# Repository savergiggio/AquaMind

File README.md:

<p align="center">
  <strong>The brain of your aquarium. 🐟</strong><br>
  Real-time monitoring: <strong>temp, pH, TDS, level, camera, AI, notifications</strong>.
</p>

<p align="center">
  <strong>🇬🇧 English</strong> · <a href="README_it.md"><strong>🇮🇹 Italiano</strong></a>
</p>

<p align="center">

</p>

<p align="center">
  <sub>
  <a href="#-features">Features</a> ·
  <a href="#-web-ui-react-dashboard">Web UI</a> ·
  <a href="#-mobile-app">Mobile app</a> ·
  <a href="#-architecture">Architecture</a> ·
  <a href="#-repository-structure">Contents</a> ·
  <a href="#-3d-models-renders">3D models</a> ·
  <a href="#-quick-start">Quick start</a> ·
  <a href="#-api">API</a> ·
  <a href="#-components">Components</a> ·
  <a href="#-sponsor--pcbway">Sponsor · PCBWay</a>
  </sub>
</p>

---

# 🇬🇧 AquaMind

## 🏭 Sponsor · PCBWay

<p align="center">
  
</p>

A big thanks to  **[PCBWay](https://pcbway.com)** for supporting the project and taking care of the PCB fabrication for AquaMind.
They manufactured the AquaMind board directly from the Gerber files and production data available in pcb/kicad/.
I was really happy with how the board turned out. The overall finish was very clean, the silkscreen was sharp, and the drilling and routing looked precise.

The whole production process was straightforward, and the board arrived quickly and well made. Most importantly, the final result matched the design very closely, which gave me much more confidence in the hardware.
Overall, I had a very positive experience with PCBWay. Seeing AquaMind go from a PCB layout on screen to a real, professionally manufactured board was one of the most satisfying parts of the project.

Thanks again to PCBWay for supporting AquaMind and helping turn the design into a real PCB.

- 📂 Fab-ready Gerbers: `pcb/kicad/gerber/`
- 📋 BOM + positions + IPC netlist: `pcb/kicad/production/`
- 🧊 3D model of the board: `pcb/kicad/AquaMind.step`

Want to build the board? Upload the Gerber set to PCBWay — the project thanks
everyone who supports the hardware pipeline. 🐟

---

## 🐟 What is AquaMind

**AquaMind** is a complete, open-source system for monitoring and controlling a
fish tank. A microcontroller reads the submerged sensors, a Raspberry Pi acts as the
central brain (history, video, AI and notifications) and a web dashboard + mobile app
let you keep an eye on everything, even from afar.

The project covers **the entire chain**: from the sensor firmware, to the custom PCB,
to the 3D-printed case, all the way to the Docker backend and the React frontend.

### 📸 The built prototype · 3D-printed case + custom PCB

A photo tour of the **physically built prototype**: PCB fabricated by PCBWay, 3D-printed enclosure and all the components. **Click any photo to open it full size.**

<table>
  <tr>
    <td align="center"><br><sub>🏭 PCB fabricated by PCBWay</sub></td>
    <td align="center"><br><sub>🧩 Components &amp; JST connectors</sub></td>
    <td align="center"><br><sub>🔌 Wired sensors + ESP32</sub></td>
  </tr>
  <tr>
    <td align="center"><br><sub>🧊 3D-printed enclosure + PCB</sub></td>
    <td align="center"><br><sub>🖥️ Enclosure with OLED display</sub></td>
    <td align="center"><br><sub>🐟 3D-printed lid "AQUAMIND"</sub></td>
  </tr>
  <tr>
    <td align="center"><br><sub>🏷️ Front panel · TEMP · PH · TDS · LEVEL</sub></td>
    <td align="center"><br><sub>📂 Open enclosure, PCB inside</sub></td>
    <td align="center"><br><sub>🐠 The prototype in the aquarium</sub></td>
  </tr>
</table>

### ⚙️ Features

| Area | What it does |
|------|-------------|
| 📷 **Video** | **IMX179** camera (8MP, 1080p) inside a **repurposed transparent garden sphere**, live MJPEG streaming |
| 💡 **Controls** | Lights, pump, skimmer, heater, feeder — from web and app |
| 📅 **Scheduler** | Automatic on/off schedules for every device |
| 🤖 **AI** | **Google Gemini** integration for diagnostics and control |
| 🔔 **Notifications** | **ntfy** and **Telegram** alerts when a parameter goes out of range |
| 📈 **History** | Archived data with browsable history (`/sensors/history` API) |
| 🖥️ **Web UI** | **React + Vite + Tailwind** dashboard served by Nginx |
| 📱 **Mobile app** | Android app riding on the **same REST API** (sensors, video, AI, guides, backup) |
| 🧩 **Home Assistant** | Custom component for **Chihiros** lights (BLE) |

---

## 🖥️ Web UI (React dashboard)

The React dashboard is the control center: live video from the underwater sphere,
real-time sensor cards, AI agent, manual controls, schedules, maintenance calendar,
fish inventory and full history. **Click any screenshot to open it full size.**

<table>
  <tr>
    <td align="center" colspan="2"><br><sub>📷 <b>Dashboard</b> — live video, sensors (TEMP · PH · TDS · LEVEL), AquaMind AI agent, manual controls</sub></td>
  </tr>
  <tr>
    <td align="center"><br><sub>📅 <b>Maintenance</b> — calendar with scheduled water changes and events</sub></td>
    <td align="center"><br><sub>💧 <b>Water parameters</b> — full analysis, hardness, complete recipe</sub></td>
  </tr>
  <tr>
    <td align="center"><br><sub>🐠 <b>Fish inventory</b> — species, quantity, food and last feeding</sub></td>
    <td align="center"><br><sub>📈 <b>History</b> — telemetry charts with min/max/avg statistics</sub></td>
  </tr>
</table>

---

## 📱 Mobile app

The **Android app** rides on the same REST API as the dashboard: sensor cards, live video,
AI assistant, treatment guides, tank management and backup — right from the phone.
**Tap any screenshot to open it full size.**

<table>
  <tr>
    <td align="center"><br><sub>🏠 <b>Home</b> — sensor cards (TEMP · PH · TDS · LEVEL), trend charts, AI agent</sub></td>
    <td align="center"><br><sub>📖 <b>Guides &amp; recipes</b> — disease treatments saved per tank</sub></td>
    <td align="center"><br><sub>⚙️ <b>Management</b> — add aquarium, tank manager, backup export/import</sub></td>
    <td align="center"><br><sub>🤖 <b>AI Assistant</b> — Gemini chat, quick diagnostic</sub></td>
    <td align="center"><br><sub>🩺 <b>Full diagnostic</b> — pH, nitrogen cycle, GH/KH, TDS, fish compatibility</sub></td>
  </tr>
</table>

All 12 app screenshots are in [`images/`](images/).

---

## 🧠 Architecture

The flow is simple: the **ESP32-S3** reads the sensors and publishes them as JSON over
serial; the **Raspberry Pi** (in Docker) receives and stores them, acts as the hub for
video and controls, and pushes events to the dashboard, the app and the notification
channels.

```mermaid
flowchart LR
  subgraph Tank
    S1[DS18B20]
    S2[PH-4502C]
    S3[TDS]
    S4[RCWL-1670]
    CAM[IMX179]
  end
  S1 --> ESP[ESP32-S3]
  S2 --> ESP
  S3 --> ESP
  S4 --> ESP
  ESP -- serial JSON --> RPI[Raspberry Pi]
  CAM -- MJPEG --> RPI
  RPI --> DB[(SQLite)]
  RPI --> WEB[React Dashboard]
  RPI --> APP[Mobile App]
  RPI --> AI[Gemini AI]
  RPI --> NTF[ntfy / Telegram]
```

---

## 📦 Repository structure

The repo is organized in 4 areas, one per "layer" of the project:

```
.
├── 3D/
│   ├── case/            #    Enclosure: base, lid, sensor mounts, spacer, cap
│   ├── display/         #    display_aquamind + 53 mm glass mount (SLDPRT/STEP)
│   └── completo/        #    Main assemblies as GLB (viewable in the browser)
├── codice/
│   ├── esp32-s3/        # Sensor firmware (ESP32-S3, v2.0.0-S3)
│   └── raspberry/       # Full dockerized system (backend + frontend)
│       ├── backend/     #   Node.js: API, history, video, AI, notifications, Chihiros
│       ├── frontend/    #   React + Vite + Tailwind (dashboard)
│       ├── docs/        #   Setup notes (Bluetooth, etc.)
│       └── docker-compose.yml
├── pcb/
│   └── kicad/           # KiCad project: sch, pcb, gerber, BOM, netlist, positions
│       ├── gerber/      #   Production files (fab-ready)
│       └── production/  #   BOM, designators, IPC netlist, positions
├── rendering/           # Full-system renderings
├── images/              # Built-prototype photos · Web UI screens · mobile app screens
└── docs/                # Page images and banner
```

### 🧊 1 · Case and 3D models

The mechanics are designed in **SolidWorks** (`.SLDPRT` sources) and exported as
**STEP** (neutral format for CAD/verification). In the repo you will find:

- **`3D/case/`** — the complete enclosure: base, lid, sensor mounts, spacer, cap and
  the full assembly (`AquaMind.step`).
- **`3D/display/`** — the **display housing** (`display_aquamind`) and the **53 mm
  glass mount**, the bracket that fixes the camera sphere to the tank glass.
- **`3D/completo/`** — the **main assemblies as GLB**, viewable directly in the
  browser.

> 💡 `.SLDPRT` are the SolidWorks sources, `.STEP` is the neutral exchange format.

### 🔲 2 · Sensor firmware (ESP32-S3)

`codice/esp32-s3/Aquamind-s3.ino` — firmware that reads the 4 sensors and publishes
them as JSON over serial/UART every 2 seconds, with a **local OLED display** and
**EEPROM-based calibration** (pH offset, TDS coefficient, level range).

- **DS18B20** → temperature (OneWire)
- **PH-4502C** → pH (ADC)
- **TDS** → salinity (ADC)
- **RCWL-1670** → water level (mmWave)
- **SSD1306** → 128×64 OLED display (I²C)

### 🍓 3 · Raspberry Pi system (Docker)

`codice/raspberry/` is the complete **dockerized** system (backend + frontend in
containers):

- **`backend/`** — **Node.js** server: REST API, serial ingest, MJPEG video streaming,
  SQLite history, controls, scheduler, **Gemini AI** proxy, **ntfy/Telegram**
  notifications and a daemon for the **Chihiros** lights (BLE).
- **`frontend/`** — **React + Vite + Tailwind** dashboard, served by **Nginx**.
- **`docker-compose.yml`** — orchestrates the two services (backend on `host`
  network for USB/BLE, frontend on port 80).
#### What the backend does (subsystems)

| Subsystem | How it works |
|----------------|---------------|
| **REST API** | Express (`server.js`) exposes the `/api/*` endpoints for the dashboard and the mobile app |
| **WebSocket** | `ws` on `/ws` → live push of sensors, device states and alerts to the dashboard |
| **Serial ingest** | `serialport` reads the JSON frames from the ESP32; one port per tank (`tankSerialPorts`) |
| **History** | `better-sqlite3` with `sensors`, `alert_log`, `schedules`, `chihiros_devices`, `maintenance_log`, `water_parameters`, `fish_inventory` tables (+ auto migrations) |
| **Video** | `child_process` + `ffmpeg` → MJPEG stream from `/dev/video0` (`/api/stream`) |
| **Scheduler** | Automatic device on/off, with active-devices lookup (`/api/schedules/active-devices`) |
| **Alerts** | Configurable thresholds and deltas, event log, notification test (`/api/alerts/*`) |
| **Notifications** | Push to **ntfy** and **Telegram** when a parameter goes out of range |
| **Chihiros BLE** | Python daemon (`chihiros_daemon.py` + `bleak`) handles scan, on/off, brightness, RGB, channels, schedules and auto-mode |
| **AI** | **Gemini** proxy (`/api/gemini`) with saved conversations and recipes |
| **Multi-tank** | Tank CRUD, remote calibration, camera settings, config export/import |
| **Firmware** | ESP32 firmware flashing over serial upload (`/api/tanks/:id/firmware`) |
| **Backup** | Database export/import (`/api/backup`, `/api/restore`) |

<details>
<summary><b>Quick start</b></summary>

```bash
cd codice/raspberry
cp backend/.env.example backend/.env   # add GEMINI_API_KEY, tokens, etc.
docker-compose build
docker-compose up -d
# Dashboard: http://<raspberry-ip>/
```

</details>

### 🛠️ 4 · PCB (KiCad)

`pcb/kicad/` contains the complete **KiCad** project of the AquaMind board:

- `AquaMind.kicad_sch` / `AquaMind.kicad_pcb` — schematic and PCB layout (2 layers)
- `gerber/` — complete production set (Cu, mask, silkscreen, paste, edge cuts, drill)
- `production/` — **BOM**, **designators**, **IPC netlist** and **positions** for
 manufacturing
- `AquaMind.step` — 3D model of the PCB

> ℹ️ In the BOM the board uses the **ESP32-C3 SuperMini** module (`U1`); the firmware
> in `codice/esp32-s3/Aquamind-s3.ino` is written for the **ESP32-S3 DevKit** — pins
> are configurable at the top of the file.

> 🏭 **The PCBs of this project are fabricated by [PCBWay](https://pcbway.com)** —
> the files in `gerber/` and `production/` are fab-order ready.

## 🧊 3D models (renders)

Renders of the **CAD 3D models** (from the GLB assemblies in `3D/`) — these are **not**
photos of the built hardware, the physical prototype is in the section above:

<table>
  <tr>
    <td align="center"><br><sub>🧊 Board + sensors assembly</sub></td>
    <td align="center"><br><sub>📷 Camera sphere + 53 mm mount</sub></td>
    <td align="center"><br><sub>🛠️ AquaMind PCB</sub></td>
  </tr>
</table>

### 📷 The underwater sphere

To house the camera underwater, a **transparent garden sphere** was purchased — one of
those solar-panel LED globes used for garden lighting — and **repurposed** for this
purpose: inside it sits the **IMX179** camera (8 MP, 1080p, 1/3.2″ CMOS), and the
sphere is fixed to the tank glass with the **53 mm mount** (sources in `3D/display/`).

---

## 🚀 Quick start

```bash
# 1. Clone the repo
git clone https://github.com/<your-username>/AquaMind.git
cd AquaMind

# 2. Start the Raspberry system (Docker)
cd codice/raspberry
cp backend/.env.example backend/.env
docker-compose build && docker-compose up -d

# 3. Flash the ESP32-S3 firmware (from Arduino IDE)
#    Board: ESP32S3 Dev Module · Port: /dev/ttyUSB*
```

Open the dashboard at `http://<raspberry-ip>` and you are up and running. 🐠

---

## 🔌 API

| Endpoint | Method | Description |
|----------|--------|-------------|
| `/api/sensors` | GET | Current sensor data |
| `/api/sensors/history?hours=24` | GET | Data history |
| `/api/controls` | GET / POST | Device state / control |
| `/api/schedules` | GET / POST | Schedules |
| `/api/schedules/:id` | PUT / DELETE | Update / delete schedule |
| `/api/stream` | GET | MJPEG video stream |
| `/api/status` | GET | System status |
| `/api/gemini` | POST | Gemini AI proxy |

Example:

```bash
curl http://raspberry/api/sensors
# {"temp":25.4,"ph":8.2,"tds":120,"level":98,"fw_version":"2.0.0-S3"}

curl -X POST http://raspberry/api/controls \
  -H "Content-Type: application/json" \
  -d '{"device":"mainLight","state":true}'
```

---

## 🖼️ Components

The hardware components at the heart of the project:

| | | |
|:---:|:---:|:---:|
|  |  |  |
| 🎥 **IMX179** — 8MP camera<br>night-vision in the underwater sphere | 🧪 **TDS** — salinity probe<br>ADC, EEPROM calibration | 🔬 **PH-4502C** — pH probe<br>ADC, EEPROM offset |
 |  |  |  |
| 🌡️ **DS18B20** — temperature probe<br>OneWire bus | 📶 **RCWL-1670** — mmWave module<br>water-level detection | 🖥️ **OLED SSD1306** — local display<br>128×64 I²C |
|  |  | |
| 🧠 **ESP32-S3** — microcontroller<br>sensor reading + OLED | 🍓 **Raspberry Pi** — central hub<br>API, history, video, AI | |

---

## 📄 License

[MIT](LICENSE) — fork it, improve it, share it. 🐟

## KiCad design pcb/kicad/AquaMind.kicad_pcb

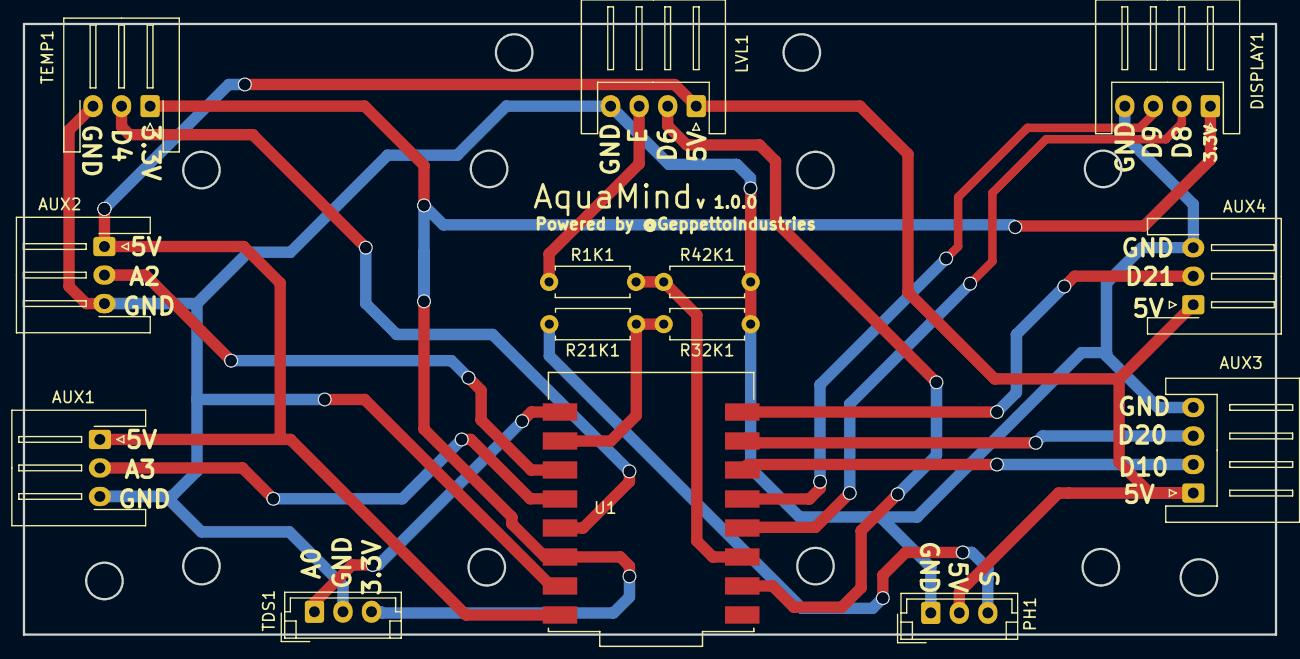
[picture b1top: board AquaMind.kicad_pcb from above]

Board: 2 copper layers, 109.7 x 53.5 mm, 14 parts (0 on the bottom side), 17 nets.

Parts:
AUX1: AUX1; JST_XH_S3B-XH-A-1_1x03_P2.50mm_Horizontal
AUX2: AUX2; JST_XH_S3B-XH-A-1_1x03_P2.50mm_Horizontal
AUX3: AUX3; JST_XH_S4B-XH-A_1x04_P2.50mm_Horizontal
AUX4: AUX4; JST_XH_S3B-XH-A-1_1x03_P2.50mm_Horizontal
DISPLAY1: DISPLAY; JST_XH_S4B-XH-A_1x04_P2.50mm_Horizontal
LVL1: LVL; JST_XH_S4B-XH-A_1x04_P2.50mm_Horizontal
PH1: PH; JST_EH_B3B-EH-A_1x03_P2.50mm_Vertical
R1K1, R21K1: 1K; R_Axial_DIN0207_L6.3mm_D2.5mm_P7.62mm_Horizontal
R32K1, R42K1: 2K; R_Axial_DIN0207_L6.3mm_D2.5mm_P7.62mm_Horizontal
TDS1: TDS; JST_EH_B3B-EH-A_1x03_P2.50mm_Vertical
TEMP1: TEMP; JST_XH_S3B-XH-A-1_1x03_P2.50mm_Horizontal
U1: ESP32-C3_SUPERMINI_SMD; MODULE_ESP32-C3_SUPERMINI

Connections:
+3.3V: DISPLAY1.1, TDS1.3, TEMP1.1, U1.3.3 (3V3)
+5V: AUX1.1, AUX2.1, AUX3.1, AUX4.1, LVL1.1, PH1.2, U1.5V
A0: TDS1.1, U1.0 (GPIO0)
A1: R21K1.2, R32K1.1, U1.1 (GPIO1)
A2: AUX2.2, U1.2 (GPIO2)
A3: AUX1.2, U1.3 (GPIO3)
D4: TEMP1.2, U1.4 (GPIO4)
D6: LVL1.2, U1.6 (GPIO6)
D7: R1K1.2, R42K1.1, U1.7 (GPIO7)
D8: DISPLAY1.2, U1.8 (GPIO8)
D9: DISPLAY1.3, U1.9 (GPIO9)
D10: AUX3.2, U1.10 (GPIO10)
D20: AUX3.3, U1.20 (GPIO20)
D21: AUX4.2, U1.21 (GPIO21)
GND: AUX1.3, AUX2.3, AUX3.4, AUX4.3, DISPLAY1.4, LVL1.4, PH1.1, R32K1.2, R42K1.2, TDS1.2, TEMP1.3, U1.G (GND)
unnamed: LVL1.3, R1K1.1
unnamed: PH1.3, R21K1.1
